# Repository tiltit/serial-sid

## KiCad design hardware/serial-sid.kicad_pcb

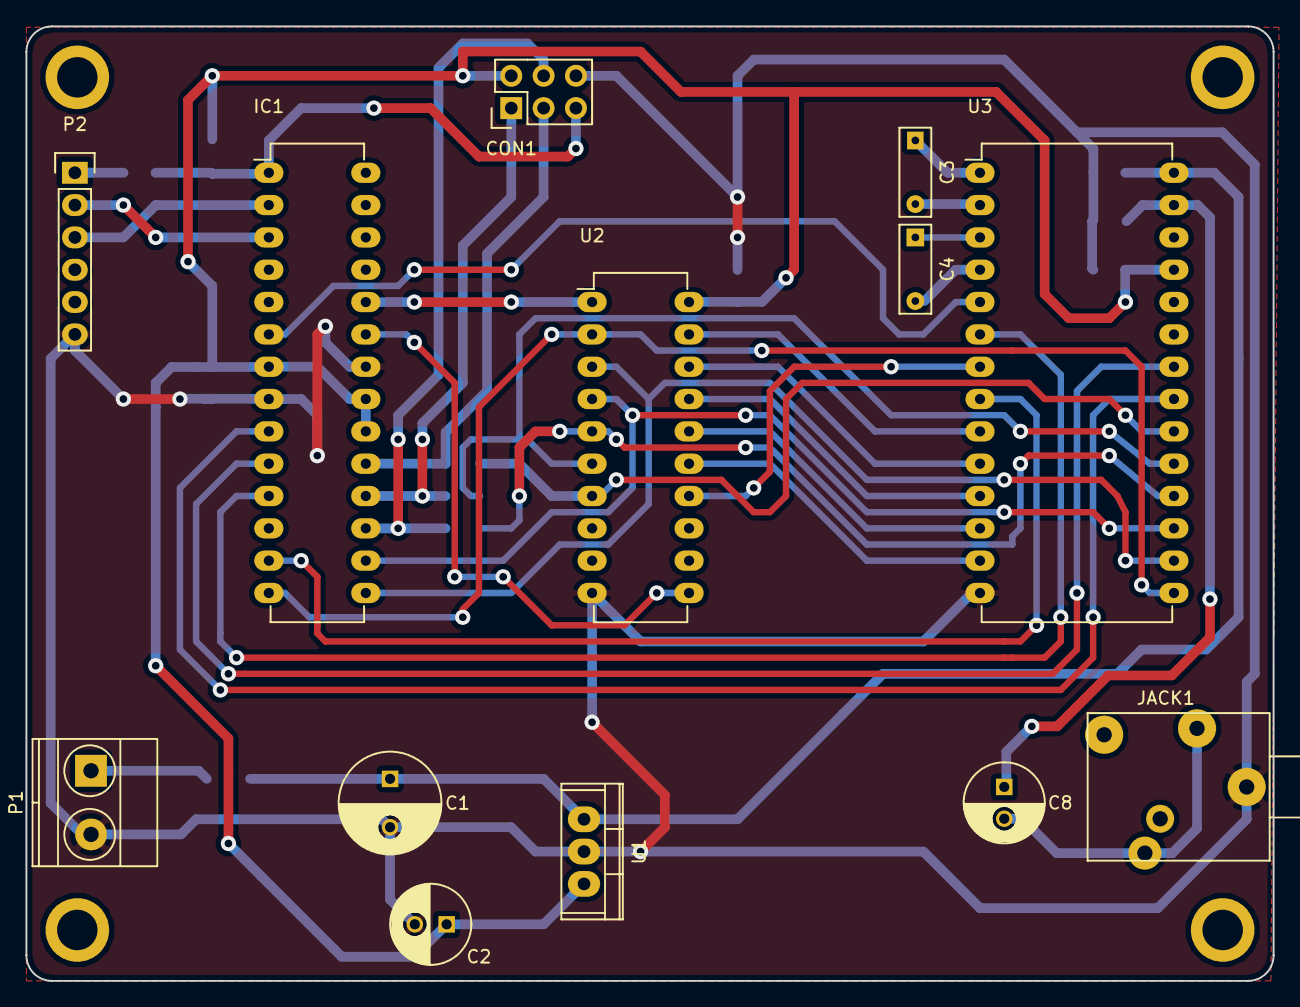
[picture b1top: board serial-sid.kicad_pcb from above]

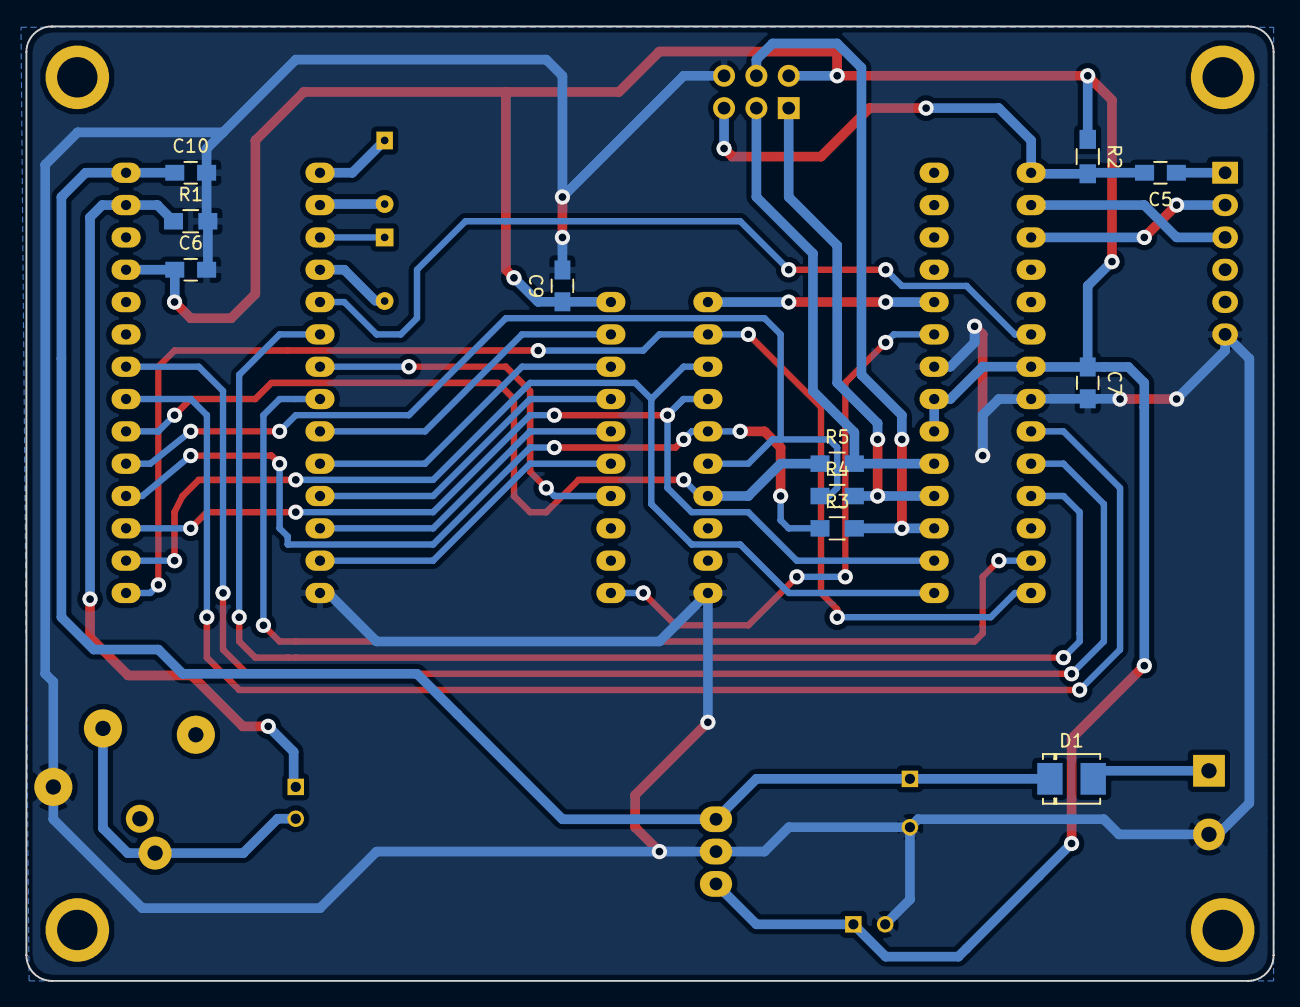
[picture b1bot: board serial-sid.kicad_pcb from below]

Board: 2 copper layers, 98.0 x 75.0 mm, 24 parts (11 on the bottom side), 36 nets.

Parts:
C1: 47uf; C_Radial_D8_L13_P3.8
C2: 4.7uf; C_Radial_D6.3_L11.2_P2.5
C3, C4: 2n2; C_Rect_L7_W2.5_P5
C5, C6, C9: 100n; C_0805_HandSoldering
C7, C10: 100nf; C_0805_HandSoldering
C8: 10uf; C_Radial_D6.3_L11.2_P2.5
CON1: AVR-ISP-6; Pin_Header_Straight_2x03
D1: D; DO-214BA
IC1: ATMEGA328P-P; DIP-28_W7.62mm_LongPads
JACK1: JACK_3.5MM-3P; 3.5mm_jack_5pin
P1: 12V Input; TerminalBlock_Pheonix_MKDS1.5-2pol
P2: CONN_01X06; Pin_Header_Straight_1x06
R1, R3, R4, R5: 1K; R_0805_HandSoldering
R2: 10K; R_0805_HandSoldering
U1: 7805; TO-220
U2: 74LS574; DIP-20_W7.62mm_LongPads
U3: MOS6581; DIP-28_W15.24mm_LongPads

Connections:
A0: U2.19, U3.9
A1: U2.18, U3.10
A2: U2.17, U3.11
A3: U2.16, U3.12
A4: U2.15, U3.13
CS: IC1.13, U3.8
D0: IC1.14, U2.2, U3.15
D1: IC1.15, U2.3, U3.16
D2: IC1.16, U2.4, U3.17
D3: R3.1, U2.5, U3.18
D4: R4.1, U2.6, U3.19
D5: R5.1, U2.7, U3.20
D6: IC1.9, U3.21
D7: IC1.10, U3.22
GND: C1.2, C2.2, C6.2, C7.2, C9.2, C10.2, CON1.6, IC1.8, IC1.22, JACK1.1, P1.2, P2.6, R1.2, U1.GND, U2.10, U3.14
MISO: CON1.1, IC1.18, R4.2
MOSI: CON1.4, IC1.17, R3.2
unnamed: C3.1, U3.1
unnamed: C3.2, U3.2
unnamed: C4.1, U3.3
unnamed: C4.2, U3.4
unnamed: C5.1, P2.1
unnamed: C8.1, R1.1, U3.27
unnamed: C8.2, JACK1.2, JACK1.3
unnamed: D1.2, P1.1
unnamed: IC1.23, U2.11
unnamed: IC1.24, U2.1
RESET: C5.2, CON1.5, IC1.1, R2.2
RW: U2.14, U3.7
RX: IC1.2, P2.3
SCK: CON1.3, IC1.19, R5.2
SID_CLOCK: IC1.11, U3.6
SID_RESET: IC1.6, U3.5
TX: IC1.3, P2.2
VCC: C2.1, C6.1, C7.1, C9.1, CON1.2, IC1.7, IC1.20, IC1.21, R2.1, U1.VO, U2.20, U3.25
VDD: C1.1, C10.1, D1.1, U1.VI, U3.28
